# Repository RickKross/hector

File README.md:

# hector
Hector is a 38-key column staggered keyboard with HE magnetic sensors

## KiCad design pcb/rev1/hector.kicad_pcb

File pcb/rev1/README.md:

# keyboard
WIP Split Keyboard with HE

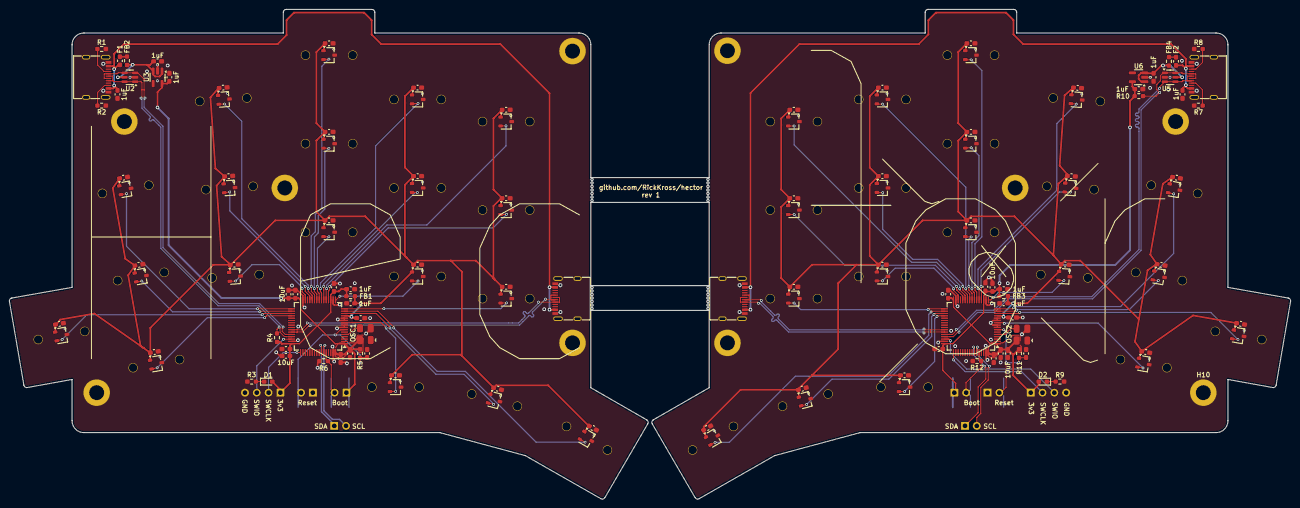
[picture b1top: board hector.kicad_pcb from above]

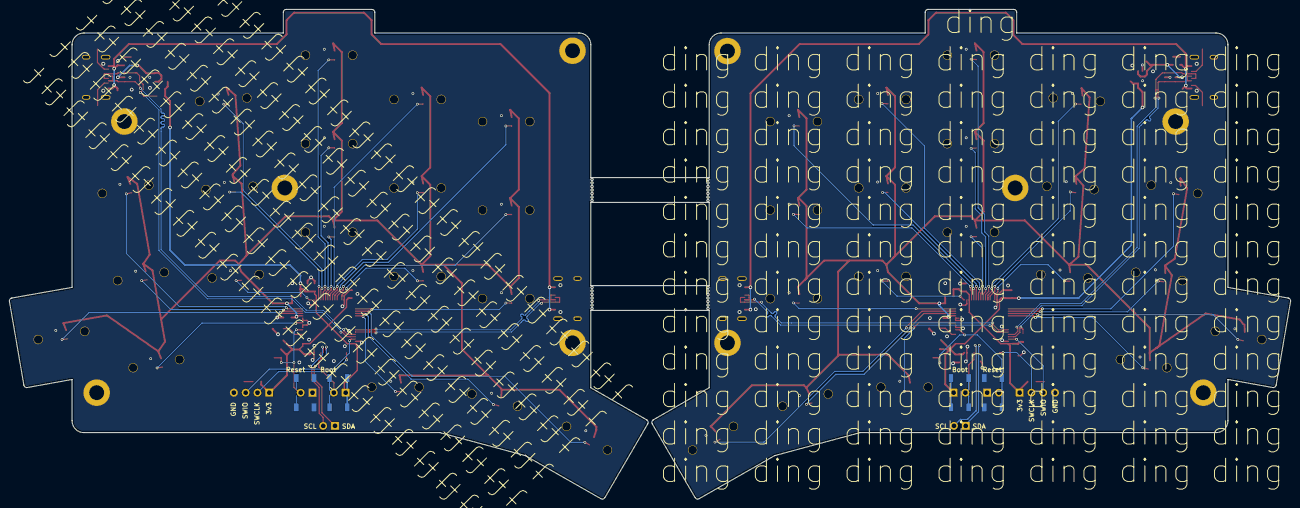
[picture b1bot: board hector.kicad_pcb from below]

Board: 2 copper layers, 275.7 x 105.4 mm, 196 parts (5 on the bottom side), 73 nets.

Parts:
C1, C13, C33, C45: 10uF; C_0603_1608Metric_Pad1.08x0.95mm_HandSolder
C2, C3, C4, C5, C6, C7, C12, C14, C15, C16, C17, C18, C19, C20, C21, C22, C23, C24, C25, C26, C27, C28, C29, C30, C31, C32, C34, C35, C36, C37, C38, C39, C44, C46, C47, C48, C49, C50, C51, C52, C53, C54, C55, C56, C57, C58, C59, C60, C61, C62, C63, C64: 100nF; C_0603_1608Metric_Pad1.08x0.95mm_HandSolder
C8, C9, C10, C11, C40, C41, C42, C43, C65, C66: 1uF; C_0603_1608Metric_Pad1.08x0.95mm_HandSolder
D1, D2: RED; LED_0603_1608Metric_Pad1.05x0.95mm_HandSolder
F1, F2: 350mA; Fuse_0603_1608Metric_Pad1.05x0.95mm_HandSolder
FB1, FB2, FB3, FB4: BLM18KG121TN1D; R_0603_1608Metric_Pad0.98x0.95mm_HandSolder
H1, H2, H3, H4, H5, H6, H7, H8, H9, H10: MountingHole_Pad; MountingHole_3.2mm_M3_ISO7380_Pad
HS1, HS2, HS3, HS4, HS5, HS6, HS7, HS8, HS9, HS10, HS11, HS12, HS13, HS14, HS15, HS16, HS17, HS18, HS19, HS20, HS21, HS22, HS23, HS24, HS25, HS26, HS27, HS28, HS29, HS30, HS31, HS32, HS33, HS34, HS35, HS36, HS37, HS38: SS49E; SOT-23W
J1, J2, J8, J9: USB_C; USB_C_Receptacle_G-Switch_GT-USB-7010ASV
J3, J4, J5, J10, J11, J12: PinHeader_1x02_P2.54mm_Vertical
J6, J13: Conn_01x04_Pin; PinHeader_1x04_P2.54mm_Vertical
MX1, MX2, MX3, MX4, MX5, MX6, MX7, MX8, MX9, MX10, MX11, MX12, MX13, MX14, MX15, MX16, MX17, MX18, MX19, MX20, MX21, MX22, MX23, MX24, MX25, MX26, MX27, MX28, MX29, MX30, MX31, MX32, MX33, MX34, MX35, MX36, MX37, MX38: MX 1.00u
OSC1, OSC2: 8MHz; SMD5032-4P
R1, R2, R3, R7, R8, R9: 5.1k; R_0603_1608Metric_Pad0.98x0.95mm_HandSolder
R4, R10: 1.5k; R_0603_1608Metric_Pad0.98x0.95mm_HandSolder
R5, R6, R11, R12: 40k; R_0603_1608Metric_Pad0.98x0.95mm_HandSolder
SW1, SW2, SW4, SW5: SW_Push; SW_SPST_TL3342
U1, U4: STM32F303RETx; LQFP-64_10x10mm_P0.5mm
U2, U5: USBLC6-2SC6; SOT-23-6
U3, U6: RT9013-33GB; SOT-23-5_HandSoldering

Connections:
+3.3VA: C7.1, C8.1, C14.2, C15.2, C16.2, C17.2, C18.2, C19.2, C20.2, C21.2, C22.2, C23.2, C24.2, C25.2, C26.2, C27.2, C28.2, C29.2, C30.2, C31.2, C32.2, C39.1, C40.1, C46.2, C47.2, C48.2, C49.2, C50.2, C51.2, C52.2, C53.2, C54.2, C55.2, C56.2, C57.2, C58.2, C59.2, C60.2, C61.2, C62.2, C63.2, C64.2, FB1.1, FB3.1, HS1.1 (VCC), HS2.1 (VCC), HS3.1 (VCC), HS4.1 (VCC), HS5.1 (VCC), HS6.1 (VCC), HS7.1 (VCC), HS8.1 (VCC), HS9.1 (VCC), HS10.1 (VCC), HS11.1 (VCC), HS12.1 (VCC), HS13.1 (VCC), HS14.1 (VCC), HS15.1 (VCC), HS16.1 (VCC), HS17.1 (VCC), HS18.1 (VCC), HS19.1 (VCC), HS20.1 (VCC), HS21.1 (VCC), HS22.1 (VCC), HS23.1 (VCC), HS24.1 (VCC), HS25.1 (VCC), HS26.1 (VCC), HS27.1 (VCC), HS28.1 (VCC), HS29.1 (VCC), HS30.1 (VCC), HS31.1 (VCC), HS32.1 (VCC), HS33.1 (VCC), HS34.1 (VCC), HS35.1 (VCC), HS36.1 (VCC), HS37.1 (VCC), HS38.1 (VCC), U1.13 (VDDA), U4.13 (VDDA)
+3V3: C1.1, C2.1, C3.1, C4.1, C5.1, C6.1, C9.1, C11.1, C13.2, C33.1, C34.1, C35.1, C36.1, C37.1, C38.1, C41.1, C43.1, C45.2, D1.2 (A), D2.2 (A), FB1.2, FB3.2, J5.1, J6.1, J12.1, J13.1, OSC1.4 (VDD), OSC2.4 (VDD), R4.2, R5.2, R10.2, R11.2, SW2.1, SW5.1, U1.1 (VBAT), U1.19 (VDD), U1.32 (VDD), U1.48 (VDD), U1.64 (VDD), U3.5 (Vout), U4.1 (VBAT), U4.19 (VDD), U4.32 (VDD), U4.48 (VDD), U4.64 (VDD), U6.5 (Vout)
+5V: C10.1, C42.1, FB2.2, FB4.2, U2.5 (VBUS), U3.1 (Vin), U3.3 (EN), U5.5 (VBUS), U6.1 (Vin), U6.3 (EN)
/Left half/L:OSC_IN: OSC1.3 (Out), U1.5 (PF0)
/Right half/R:OSC_IN: OSC2.3 (Out), U4.5 (PF0)
GND: C1.2, C2.2, C3.2, C4.2, C5.2, C6.2, C7.2, C8.2, C9.2, C10.2, C11.2, C12.1, C13.1, C14.1, C15.1, C16.1, C17.1, C18.1, C19.1, C20.1, C21.1, C22.1, C23.1, C24.1, C25.1, C26.1, C27.1, C28.1, C29.1, C30.1, C31.1, C32.1, C33.2, C34.2, C35.2, C36.2, C37.2, C38.2, C39.2, C40.2, C41.2, C42.2, C43.2, C44.1, C45.1, C46.1, C47.1, C48.1, C49.1, C50.1, C51.1, C52.1, C53.1, C54.1, C55.1, C56.1, C57.1, C58.1, C59.1, C60.1, C61.1, C62.1, C63.1, C64.1, C65.2, C66.2, H1.1 (1_1), H2.1 (1_1), H3.1 (1_1), H4.1 (1_1), H5.1 (1_1), H6.1 (1_1), H7.1 (1_1), H8.1 (1_1), H9.1 (1_1), H10.1 (1_1), HS1.3 (GND), HS2.3 (GND), HS3.3 (GND), HS4.3 (GND), HS5.3 (GND), HS6.3 (GND), HS7.3 (GND), HS8.3 (GND), HS9.3 (GND), HS10.3 (GND), HS11.3 (GND), HS12.3 (GND), HS13.3 (GND), HS14.3 (GND), HS15.3 (GND), HS16.3 (GND), HS17.3 (GND), HS18.3 (GND), HS19.3 (GND), HS20.3 (GND), HS21.3 (GND), HS22.3 (GND), HS23.3 (GND), HS24.3 (GND), HS25.3 (GND), HS26.3 (GND), HS27.3 (GND), HS28.3 (GND), HS29.3 (GND), HS30.3 (GND), HS31.3 (GND), HS32.3 (GND), HS33.3 (GND), HS34.3 (GND), HS35.3 (GND), HS36.3 (GND), HS37.3 (GND), HS38.3 (GND), J1.A1 (GND), J1.A12 (GND), J1.B1 (GND), J1.B12 (GND), J1.S1 (SHIELD), J2.A1 (GND), J2.A12 (GND), J2.B1 (GND), J2.B12 (GND), J2.S1 (SHIELD), J4.1, J6.4, J8.A1 (GND), J8.A12 (GND), J8.B1 (GND), J8.B12 (GND), J8.S1 (SHIELD), J9.A1 (GND), J9.A12 (GND), J9.B1 (GND), J9.B12 (GND), J9.S1 (SHIELD), J11.1, J13.4, MX1.1 (GND_1), MX2.1 (GND_1), MX3.1 (GND_1), MX4.1 (GND_1), MX5.1 (GND_1), MX6.1 (GND_1), MX7.1 (GND_1), MX8.1 (GND_1), MX9.1 (GND_1), MX10.1 (GND_1), MX11.1 (GND_1), MX12.1 (GND_1), MX13.1 (GND_1), MX14.1 (GND_1), MX15.1 (GND_1), MX16.1 (GND_1), MX17.1 (GND_1), MX18.1 (GND_1), MX19.1 (GND_1), MX20.1 (GND_1), MX21.1 (GND_1), MX22.1 (GND_1), MX23.1 (GND_1), MX24.1 (GND_1), MX25.1 (GND_1), MX26.1 (GND_1), MX27.1 (GND_1), MX28.1 (GND_1), MX29.1 (GND_1), MX30.1 (GND_1), MX31.1 (GND_1), MX32.1 (GND_1), MX33.1 (GND_1), MX34.1 (GND_1), MX35.1 (GND_1), MX36.1 (GND_1), MX37.1 (GND_1), MX38.1 (GND_1), OSC1.2 (GND), OSC2.2 (GND), R1.2, R2.2, R3.2, R6.1, R7.2, R8.2, R9.2, R12.1, SW1.1, SW4.1, U1.8 (PC0), U1.9 (PC1), U1.11 (PC3), U1.12 (VSSA), U1.18 (VSS), U1.31 (VSS), U1.47 (VSS), U1.63 (VSS), U2.2 (GND), U3.2 (GND), U4.8 (PC0), U4.9 (PC1), U4.11 (PC3), U4.12 (VSSA), U4.18 (VSS), U4.31 (VSS), U4.47 (VSS), U4.63 (VSS), U5.2 (GND), U6.2 (GND)
L:BOOT: J5.2, R6.2, SW2.2, U1.60 (BOOT0)
L:D+: J2.A6 (D+), J2.B6 (D+), R4.1, U1.45 (PA12), U2.1 (I/O1), U2.6 (I/O1)
L:D-: J2.A7 (D-), J2.B7 (D-), U1.44 (PA11), U2.3 (I/O2), U2.4 (I/O2)
L:NRST: C12.2, J4.2, R5.1, SW1.2, U1.7 (NRST)
L:RX: J1.A6 (D+), J1.B6 (D+), U1.43 (PA10)
L:SCL: J3.2, U1.59 (PB7)
L:SDA: J3.1, U1.58 (PB6)
L:SW:0:0: HS5.2 (VOUT), U1.21 (PA5)
L:SW:0:1: HS4.2 (VOUT), U1.23 (PA7)
L:SW:0:2: HS3.2 (VOUT), U1.26 (PB0)
L:SW:0:3: HS2.2 (VOUT), U1.27 (PB1)
L:SW:0:4: HS1.2 (VOUT), U1.33 (PB12)
L:SW:1:0: HS11.2 (VOUT), U1.20 (PA4)
L:SW:1:1: HS10.2 (VOUT), U1.22 (PA6)
L:SW:1:2: HS9.2 (VOUT), U1.25 (PC5)
L:SW:1:3: HS8.2 (VOUT), U1.28 (PB2)
L:SW:1:4: HS7.2 (VOUT), U1.34 (PB13)
L:SW:1:5: HS6.2 (VOUT), U1.35 (PB14)
L:SW:2:0: HS16.2 (VOUT), U1.16 (PA2)
L:SW:2:1: HS15.2 (VOUT), U1.17 (PA3)
L:SW:2:2: HS14.2 (VOUT), U1.24 (PC4)
L:SW:2:3: HS13.2 (VOUT), U1.30 (PB11)
L:SW:2:4: HS12.2 (VOUT), U1.36 (PB15)
L:SW:3:0: HS19.2 (VOUT), U1.15 (PA1)
L:SW:3:1: HS18.2 (VOUT), U1.14 (PA0)
L:SW:3:2: HS17.2 (VOUT), U1.10 (PC2)
L:SWCLK: J6.2, U1.49 (PA14)
L:SWIO: J6.3, U1.46 (PA13)
L:TX: J1.A7 (D-), J1.B7 (D-), U1.42 (PA9)
unnamed: D1.1 (K), R3.1
unnamed: D2.1 (K), R9.1
unnamed: F1.2, FB2.1
unnamed: F2.2, FB4.1
unnamed: J2.A5 (CC1), R1.1
unnamed: J2.B5 (CC2), R2.1
unnamed: J9.A5 (CC1), R7.1
unnamed: J9.B5 (CC2), R8.1
R:BOOT: J12.2, R12.2, SW5.2, U4.60 (BOOT0)
R:D+: J9.A6 (D+), J9.B6 (D+), R10.1, U4.45 (PA12), U5.1 (I/O1), U5.6 (I/O1)
R:D-: J9.A7 (D-), J9.B7 (D-), U4.44 (PA11), U5.3 (I/O2), U5.4 (I/O2)
R:NRST: C44.2, J11.2, R11.1, SW4.2, U4.7 (NRST)
R:RX: J8.A6 (D+), J8.B6 (D+), U4.43 (PA10)
R:SCL: J10.2, U4.59 (PB7)
R:SDA: J10.1, U4.58 (PB6)
R:SW:0:0: HS20.2 (VOUT), U4.27 (PB1)
R:SW:0:1: HS21.2 (VOUT), U4.25 (PC5)
R:SW:0:2: HS22.2 (VOUT), U4.22 (PA6)
R:SW:0:3: HS23.2 (VOUT), U4.21 (PA5)
R:SW:0:4: HS24.2 (VOUT), U4.16 (PA2)
R:SW:1:0: HS25.2 (VOUT), U4.28 (PB2)
R:SW:1:1: HS26.2 (VOUT), U4.26 (PB0)
R:SW:1:2: HS27.2 (VOUT), U4.23 (PA7)
R:SW:1:3: HS28.2 (VOUT), U4.20 (PA4)
R:SW:1:4: HS29.2 (VOUT), U4.15 (PA1)
R:SW:1:5: HS30.2 (VOUT), U4.14 (PA0)
R:SW:2:0: HS31.2 (VOUT), U4.33 (PB12)
R:SW:2:1: HS32.2 (VOUT), U4.30 (PB11)
R:SW:2:2: HS33.2 (VOUT), U4.24 (PC4)
R:SW:2:3: HS34.2 (VOUT), U4.17 (PA3)
R:SW:2:4: HS35.2 (VOUT), U4.10 (PC2)
R:SW:3:0: HS36.2 (VOUT), U4.34 (PB13)
R:SW:3:1: HS37.2 (VOUT), U4.35 (PB14)
R:SW:3:2: HS38.2 (VOUT), U4.36 (PB15)
R:SWCLK: J13.2, U4.49 (PA14)
R:SWIO: J13.3, U4.46 (PA13)
R:TX: J8.A7 (D-), J8.B7 (D-), U4.42 (PA9)
VBUS: C65.1, C66.1, F1.1, F2.1, J1.A4 (VBUS), J1.A9 (VBUS), J1.B4 (VBUS), J1.B9 (VBUS), J2.A4 (VBUS), J2.A9 (VBUS), J2.B4 (VBUS), J2.B9 (VBUS), J8.A4 (VBUS), J8.A9 (VBUS), J8.B4 (VBUS), J8.B9 (VBUS), J9.A4 (VBUS), J9.A9 (VBUS), J9.B4 (VBUS), J9.B9 (VBUS)
